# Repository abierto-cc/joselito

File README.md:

# joselito
Repositorio del único amplificador que hace justicia a una de las estrellas más brillantes de la canción en habla hispana ... ¡Joselito!

Diseñado en Suecia con amor para toda la galaxia

# consigue tu kit

Si quieres conseguir el kit para montarlo, visita: https://abierto.cc/shop

# instrucciones de montaje

Puedes ver las instrucciones de montaje paso a paso en: https://sites.google.com/abierto.cc/joselito-mini

Puedes ver las instrucciones de montaje paso a paso en: https://sites.google.com/abierto.cc/joselito-embebido

# créditos

Joselito ... que nos inspira y nos guía desde las profundidades de YouTube

# autores

D. Cuartielles at abierto.cc (idea)

J. Garcia at abierto.cc (diseño en KiCAD para el Joselito mini, Joselito embebido y el Joselito Princesa Bultos)

L. Balboa at abierto.cc (gráficos)

# menciones

* Joselito ... es que no podemos dejar de pensar en el, sólo mirad esto: https://www.youtube.com/watch?v=RQnSKqZ-XVg ¿no os pone los pelos de punta?

# licencia para hardware y documentation

<br /><span xmlns:dct="http://purl.org/dc/terms/" href="http://purl.org/dc/dcmitype/Dataset" property="dct:title" rel="dct:type">Fenderino Arducaster</span> by <a xmlns:cc="http://creativecommons.org/ns#" href="https://abierto.cc" property="cc:attributionName" rel="cc:attributionURL">Proyecto Abierto</a> is licensed under a <a rel="license" href="http://creativecommons.org/licenses/by-nc-sa/4.0/">Creative Commons Reconocimiento-NoComercial-CompartirIgual 4.0 Internacional License</a>.<br />Creado a partir de la obra en <a xmlns:dct="http://purl.org/dc/terms/" href="https://github.com/abierto-cc/fenderino" rel="dct:source">https://github.com/abierto-cc/fenderino</a>

# licencia para código de ejemplos

El código está liberado bajo licencia GPLv3, se recomienda leer el fichero de licencia para más información

# abierto

Abierto es una inciativa de D. Cuartielles gracias a la generosa aportación de la Fundación PUIG por intermediación de la Fundación Ashoka de cara a contribuir a la creación de material educativo de libre acceso y circulación

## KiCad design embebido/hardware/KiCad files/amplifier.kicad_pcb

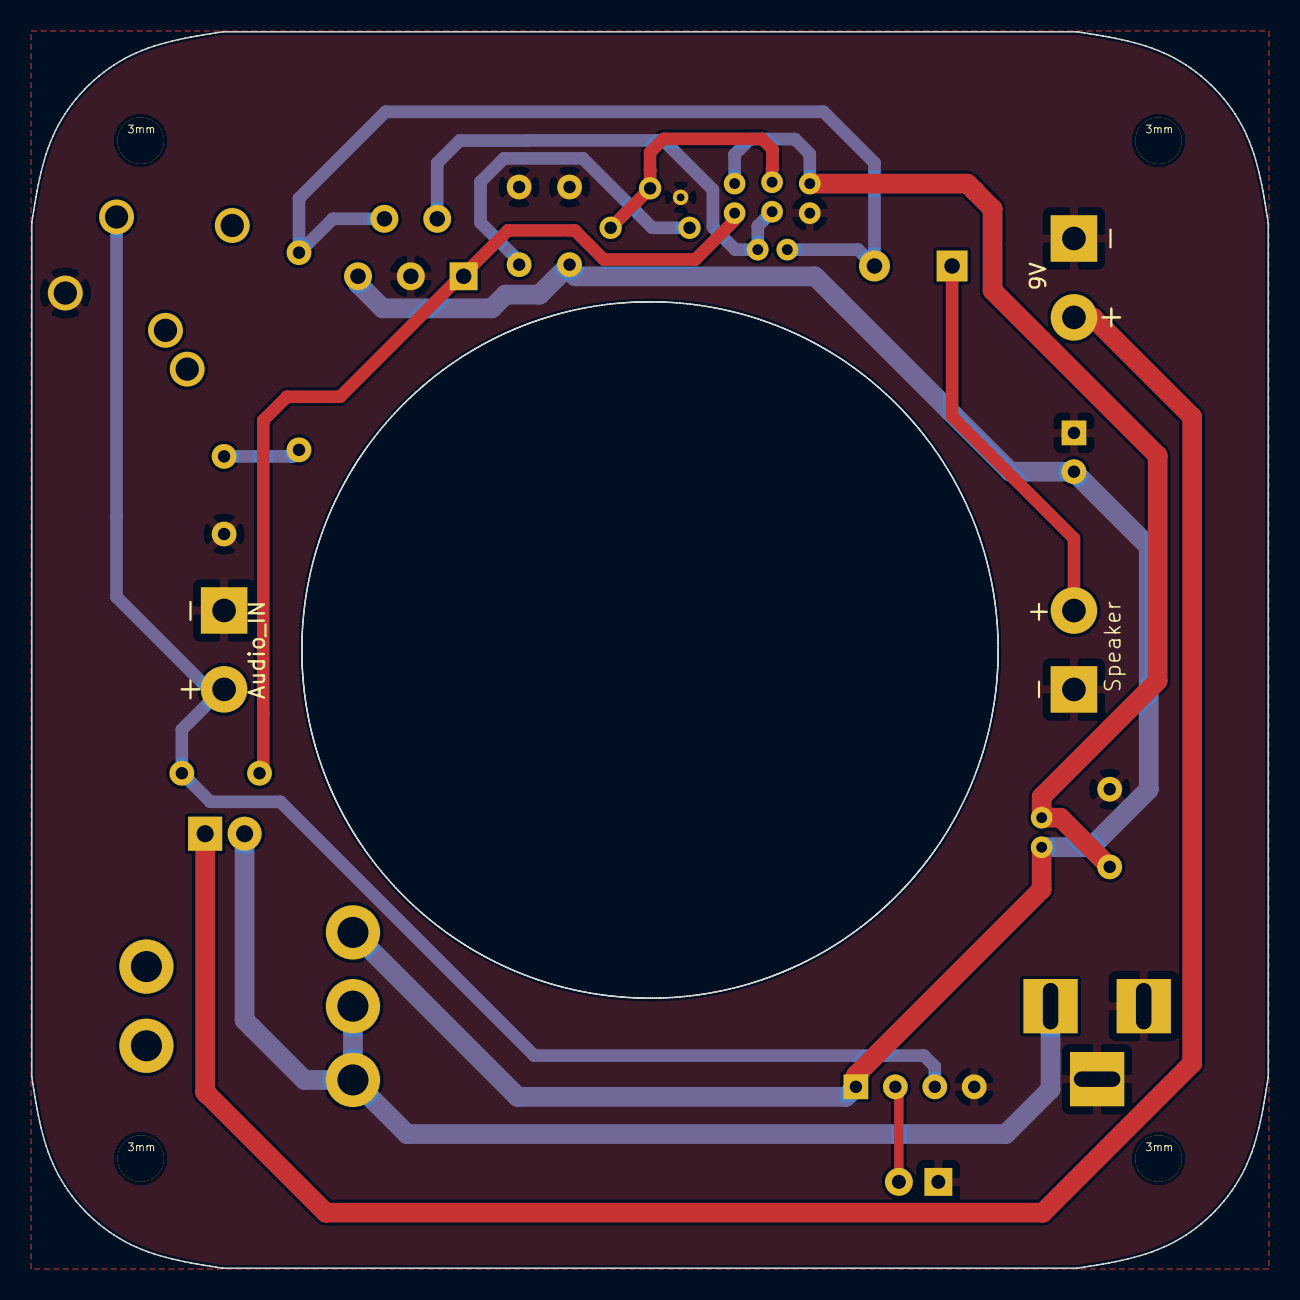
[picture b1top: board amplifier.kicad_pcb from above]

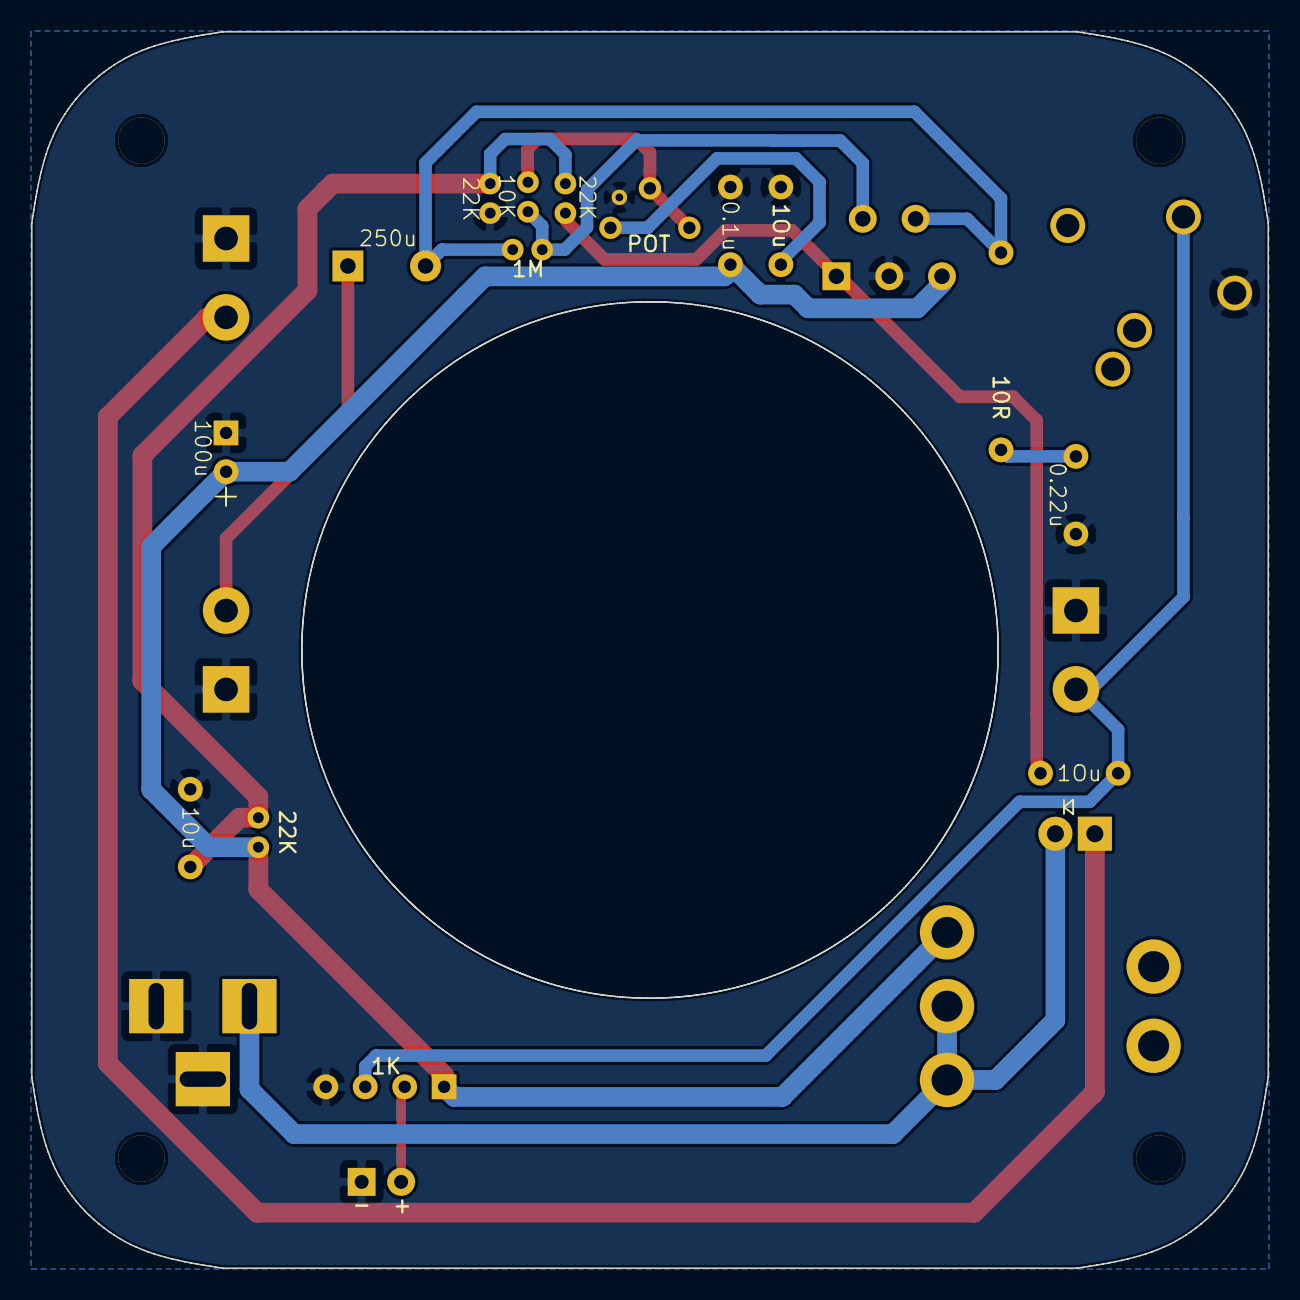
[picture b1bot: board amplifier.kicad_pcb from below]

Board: 2 copper layers, 79.6 x 79.6 mm, 24 parts (22 on the bottom side), 14 nets.

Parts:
1N1007: DIODE; D_DO-41_SOD81_P2.54mm_Vertical_AnodeUp
C1: 0.1u; C_Disc_D5.0mm_W2.5mm_P5.00mm
C2: 10u; C_Disc_D5.0mm_W2.5mm_P5.00mm
C3: 100u; CP_Radial_D6.3mm_P2.50mm
C4, C7: 1Ou; C_Disc_D5.0mm_W2.5mm_P5.00mm
C5: 250u; CP_Radial_D10.0mm_P5.00mm
C6: 0.22u; C_Rect_L7.2mm_W5.5mm_P5.00mm_FKS2_FKP2_MKS2_MKP2
D1: LED; LED_D3.0mm
J1: 12V_Charger; BARREL_JACK
J2: 9V_Battery; bornier2
J3: IN; jack_huella
J4: Speaker; bornier2
J5: Audio_In; bornier2
R1: 1K; R_Array_SIP4
R2, R3, R4: 22K; R_Axial_DIN0204_L3.6mm_D1.6mm_P1.90mm_Vertical
R5: 10k; Potentiometer_Trimmer_Vishay_T73YP_Horizontal
R6: 10R; R_Axial_DIN0309_L9.0mm_D3.2mm_P12.70mm_Horizontal
R8: 10K; R_Axial_DIN0204_L3.6mm_D1.6mm_P1.90mm_Vertical
R9: 1M; R_Axial_DIN0204_L3.6mm_D1.6mm_P1.90mm_Vertical
SW1: SW_SPDT; switch
U1: LM1875; TO-220-5_Pentawatt_Multiwatt-5_Vertical_StaggeredType1

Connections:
GND: C1.2, C2.1, C3.2, C6.1, C7.1, D1.1, J1.1, J1.2, J2.1, J3.1, J4.2, J5.2, R1.4, R2.2, U1.3
unnamed: 1N1007.1, J2.2
unnamed: 1N1007.2, J1.3, SW1.2, SW1.3
unnamed: C2.2, R2.1, R3.2, R4.1
unnamed: C4.1, R4.2, U1.1
unnamed: C4.2, J3.5, J5.1, R1.3
unnamed: C5.1, R6.1, R9.1, U1.4
unnamed: C5.2, J4.1
unnamed: C6.2, R6.2
unnamed: C7.2, R5.3
unnamed: D1.2, R1.2
unnamed: R5.1, R5.2, R8.2
unnamed: R8.1, R9.2, U1.2
VCC: C1.1, C3.1, R1.1, R3.1, SW1.1, U1.5

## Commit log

2017-10-04 Actualizado el Readme, amigos!
2017-10-04 LICENCIA ... para que luego no digan
2017-10-11 LICENCIA ... para que luego no digan
    Esqemático, PCB y gerbers del Joselito
2017-10-11 Archivos hardware
    Esquemático, PCB y Gerbers del Joselito
2017-10-11 Archivos Hardware
    Esquemáticos, PCB y Silks
2017-10-12 Amplificador Joselito
2017-10-12 Esquematicos
    Archivos png y pdf de los esquemáticos del Joselito mini
2017-10-12 Archivos KiCad
    Archivos de diseño en KiCad del Joselito mini
2017-10-12 Esquemáticos
    Archivos png y pdf de los esquemáticos del Joselito mini
2017-10-12 Gerbers
    Archivos para fabricación de PCB del Joselito mini
2017-10-12 Dimensiones
    Archivos de borde de placa en formato de componente para KiCad
2017-10-12 Esquemáticos
    Archivos png y pdf de los esquemáticos del Joselito embebido
2017-10-12 Archivos KiCad
    Archivos de diseño en KiCad del Joselito embebido
2017-10-12 Gerbers
    Archivos para fabricación de PCB del Joselito embebido
2017-10-12 Instrucciones de montaje
    Añadidas las instrucciones de montaje para el joselito-mini y el joselito-embebido
2017-10-12 Actualizado el readme... Amigos!!
    Añadidas las instrucciones de montaje para el Joselito-mini y el Joselito-embebido
2017-10-19 BOM Joselito mini
2017-10-19 BOM Joselito embebido
2017-10-31 Esquema Joselito mini
    Archivos png y pdf del esquema del Joselito mini
2017-10-31 Esquema
    Archivos png y pdf del esquema del Joselito embebido
2017-10-31 Esquema
    Archivos png y pdf del esquema del Joselito mini
